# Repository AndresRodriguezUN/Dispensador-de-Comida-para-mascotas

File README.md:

# Dispensador de Comida para mascotas 🐱 🐶
## Autores :fountain_pen:
- Diego Steven Peña Cortes :mechanic:
- Daniel Machado Roa :technologist:
- Andrés Felipe Rodríguez Contreras :office_worker:  :shipit:

Este es el repositorio del proyecto final de la asignatura Sistemas Emebidos del semestre 2021-II (Universidad Nacional de Colombia - Sede Bogotá). A continuación se mostrará el proyecto de un Dispensador de Comida conformado por una arquitectura de SoC, donde a partir de un micropocesador y diferentes periféricos se realizan operaciones que permiten al dispensador vincularse con un dispositivo movil para configurar la alimentación de la mascota.
 
 ## Proyecto :open_file_folder:
 El proyecto consiste en un dispensador de comida para mascotas que dispone de funcionalidades como la comunicación con una app movil que permite la configuración del dispositivo y el funcionamiento del mismo. Dentro del funcionamiento se encuentra la programación de los horarios de alimentación, asi como la interacción entre el usuario-dispositivo-mascota.
 
Por otro lado, el dispositivo cuenta con sensores que permiten detectar si la mascota está comiendo, además de los horarios que frecuenta el dispositivo. Y de esta manera, puede realizar un análisis de los datos y retroalimentar al usuario por medio de la actualización de los comportamientos de su mascota frente al dispositivo. Permitiendo que no se pierda la conexión que tiene el usuario con su mascota.  
 
 ## [Motivación](/Motivacion/) :thought_balloon:
 
 Con el fin de de justificar el proyecto, se definieron los viajes tanto del cliente como de la mascota y del como intervenía nuestro proyecto en cada uno de los trayectos. Esto permitio resaltar las funcionalidades directas o indirectas que debe cumplir el dispositivo a desarrollar. De esta forma se definieron los periféricos necesarios, además del módulo-procesador que se van a utilizar.

 ## Flujo de procesos

 ## [Sistema embebido](/SoC/)  :computer:
 
 El sistema embebido se definio gracias al análisis previo de las funcionalidades directas e indirectas del dispositivo, las cuales permitieron decidir los periféricos necesitados para cumplir cada una de las funcionalidades del proyecto.
 
### Periféricos

- [Pantalla OLED - I2C](/Perifericos/OLED)

- [Sensor de movimiento](/Perifericos/SensorMov)

- [Sensor infrarrojo](/Perifericos/SensorInfra)

- [Control motor - ULN2003](/Perifericos/Motor)

- [DFPlayer Mini](/Perifericos/DFPlayer)

  ## Finalidad coordinación de periféricos :nut_and_bolt:
  
  La idea es construir un dispositvo que a determinadas horas del dia ponga a disposición una porcion de comida para nuestra mascota. Esta meta se cumple con las prestaciones que nos ofrece cada uno de los componentes a ensamblar:
  
  - Tarjeta basada en ESP32: Encargada de la coordinación de los périfericos y la comunicación inalámbrica con una App.
  - App: Encargada de la retroalimentación del usuario sobre el estado de la mascota, además de la posibilidad de programar los horarios de comida que el usuario desée para su mascota.
  - Motor: Encargado de la rotación del plato en el cual estan alojadas cada una de las porciones de comida.
  - OLED: Encargado de dar una retroalimentación visual, en el dispositivo, del estado de la mascota.
  - DFP y Parlante: Encargados de reproducir una pista de audio que avise a la mascota cuando llegue la hora de comer.
  - PIR: Encargado de detectar si la mascota se acerca al dispositivo dispensador de comida, para evaluar indirectamente su estado de ánimo.
  - Infrarrojo: Encargado de detectar si la mascota ha comido alguna parte de su ración, para evaluar indirectamente su estado de ánimo.
 
Al tener todo coordinado se espera que se cumpla la finalidad del proyecto satisfactoriamente.

## [Firmware](/Firmware) :man_technologist:
El firmware de todo el proyecto se desarrolla en micropython, el cual es una version renderizada de python para poder ejecutarse en microcontroladores como lo es el ESP32. Se decidio utilizar micropython debido a su practicidad y la documentación amplia que tiene en distintos repositorios. Con respecto al ESP32 cabe destacar que se debe flashear con micropython para que todos los códigos en python que se deseen emplear se ejecuten a la perfección. Para más información sobre el manejo de micropython junto al ESP32 por favor remitase a [micropython-esp32](https://docs.micropython.org/en/latest/esp32/tutorial/index.html).

## [App](/App) :calling:

Para poder manejar el dispensador de alimentos para mascotas se creó una aplicación, la cual permita modificar los valores de tiempo en que se servirán las comidas y a su vez saber el estado en que se encuentra la mascota.

## [Diseño Caja](/Rcaja) :triangular_ruler: :package:

Se diseñó un contenedor (carcasa o caja) la cual permitiera tener el dispensador dentro de una estructura con el fin de almacenar el plato con la comida y el sistema embebido, por lo tanto, se tomaron las diferentes medidas de los periféricos para poder crear los planos en *CorelDraw* y crear la carcasa en madera gracias al proceso de corte láser.

## [Ensamble](/Ensamble) :wrench:

En esta sección se muestra el paso a paso de la unión del sistema embebido y el plato que contiene la comida con la carcasa por medio de imágenes que dan evidencia de este proceso. 

## Pruebas de funcionamiento y videos de referencia :clapper:

### Videos de referencia
Para encontrar los videos que se recomiendan a lo largo del repositorio por favor dirijase a [videos proyectos pasados](https://www.youtube.com/channel/UCFcKXg10MjH98TOnZhloZSA).

### Pruebas de funcionamiento

Se realizaron las siguientes pruebas de funcionamiento del dispositivo y la App.

- [Prueba 1](https://youtu.be/kQyHtM4AsF8).
- [Prueba 2](https://youtu.be/hgBiyUTOZwg).

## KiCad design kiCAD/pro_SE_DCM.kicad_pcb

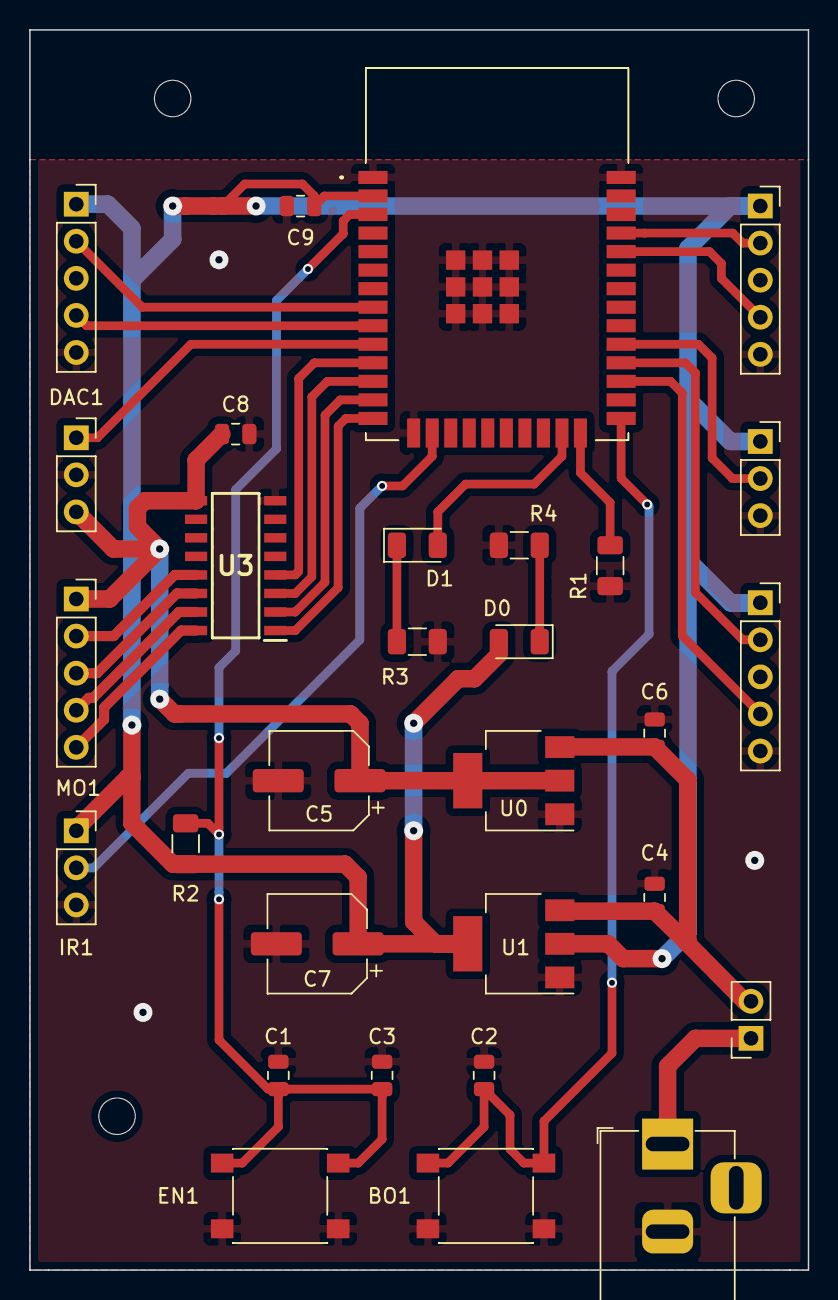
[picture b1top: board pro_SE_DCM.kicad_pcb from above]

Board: 2 copper layers, 53.3 x 85.0 mm, 30 parts (0 on the bottom side), 28 nets.

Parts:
BO1: BTN_SMD; SW_Push_1P1T_NO_6x6mm_H9.5mm
C1: 1uF/16V(20%); C_0805_2012Metric
C2, C3, C8: 1uF/16V(10%); C_0805_2012Metric
C4: 10uF/16v; C_0805_2012Metric
C5, C7: 47uF/16V; CP_Elec_6.3x5.4
C6: 10uF/16V; C_0805_2012Metric
C9: 100pF/50v; C_0805_2012Metric
D0, D1: LED; LED_1206_3216Metric
DAC1: PARLANTE; PinSocket_1x03_P2.54mm_Vertical
EN1: BTN_SMD; SW_Push_1P1T_NO_6x6mm_H9.5mm
IR1: IR-FC51; PinSocket_1x03_P2.54mm_Vertical
J0: SW_ONOFF; PinSocket_1x02_P2.54mm_Vertical
J7: JACKDC; BarrelJack_Horizontal
MO1: M_28BYJ-48; PinSocket_1x05_P2.54mm_Vertical
OL1: OLED_BPP3N0; PinSocket_1x05_P2.54mm_Vertical
PIR1: HC-SR505; PinSocket_1x03_P2.54mm_Vertical
R1: 10K(1%1-1/4w); R_1206_3216Metric
R2: 10K(1%-1/4W); R_1206_3216Metric
R3, R4: 470(5%-1/8W); R_1206_3216Metric
U0: NCP1117-5.0_SOT223; SOT-223-3_TabPin2
U1: NCP1117-3.3_SOT223; SOT-223-3_TabPin2
U2: ESP32-WROOM-32_M103QH3200PH3Q0_; ESP32WROOM32M103QH3200PH3Q0
U3: ULN2003A; SOIC127P600X175-16N
UA1: UART_CP20102; PinSocket_1x05_P2.54mm_Vertical
UA2: DFPLAYER; PinSocket_1x05_P2.54mm_Vertical

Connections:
+3V3: C7.1, C9.1, D0.2, IR1.1, OL1.1, PIR1.1, R2.1, U1.2, U2.2, UA1.1, UA2.1
+5V: C5.1, C8.1, DAC1.3, MO1.1, U0.2, U3.9
/AD_INF: IR1.2, U2.16
/DAC0: DAC1.1, U2.10
/D_PIR: PIR1.2, U2.29
/EN: C1.1, C3.1, EN1.2, R2.2, U2.3
/IO0: BO1.2, C2.1, U2.25
/IO2: R1.1, U2.24
/PD_M0: U2.11, U3.4
/PD_M1: U2.12, U3.3
/PD_M2: U2.13, U3.2
/PD_M3: U2.14, U3.1
/RDX2: U2.27, UA2.4
/RXD0: U2.34, UA1.4
/SCL0: OL1.2, U2.8
/SDA0: OL1.4, U2.9
/TXD0: U2.35, UA1.2
/TXD2: U2.28, UA2.2
/USER: D1.2, U2.23
/m0: MO1.5, U3.16
/m1: MO1.4, U3.15
/m2: MO1.3, U3.14
/m3: MO1.2, U3.13
/reg_3.3/in: C4.1, C6.1, J0.2, U0.3, U1.3
GND: BO1.1, C1.2, C2.2, C3.2, C4.2, C5.2, C6.2, C7.2, C8.2, C9.2, DAC1.2, EN1.1, IR1.3, J7.2, OL1.5, PIR1.3, R1.2, R3.2, R4.2, U0.1, U1.1, U2.1, U2.15, U2.38, U2.39, U2.40, U2.41, U2.42, U2.43, U2.44, U2.45, U2.46, U2.47, U3.8, UA1.5, UA2.5
unnamed: D0.1, R4.1
unnamed: D1.1, R3.1
unnamed: J0.1, J7.1

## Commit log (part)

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2021-11-09 Create a
2022-02-08 Create Caja
2022-02-09 Create c.
